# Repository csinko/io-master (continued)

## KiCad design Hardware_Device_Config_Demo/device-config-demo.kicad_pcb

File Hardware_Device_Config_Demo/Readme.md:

# Device Configuration Demo Board

A board to demonstrate the parts of the overall design that need to be configured when setting up a protocol for operation.

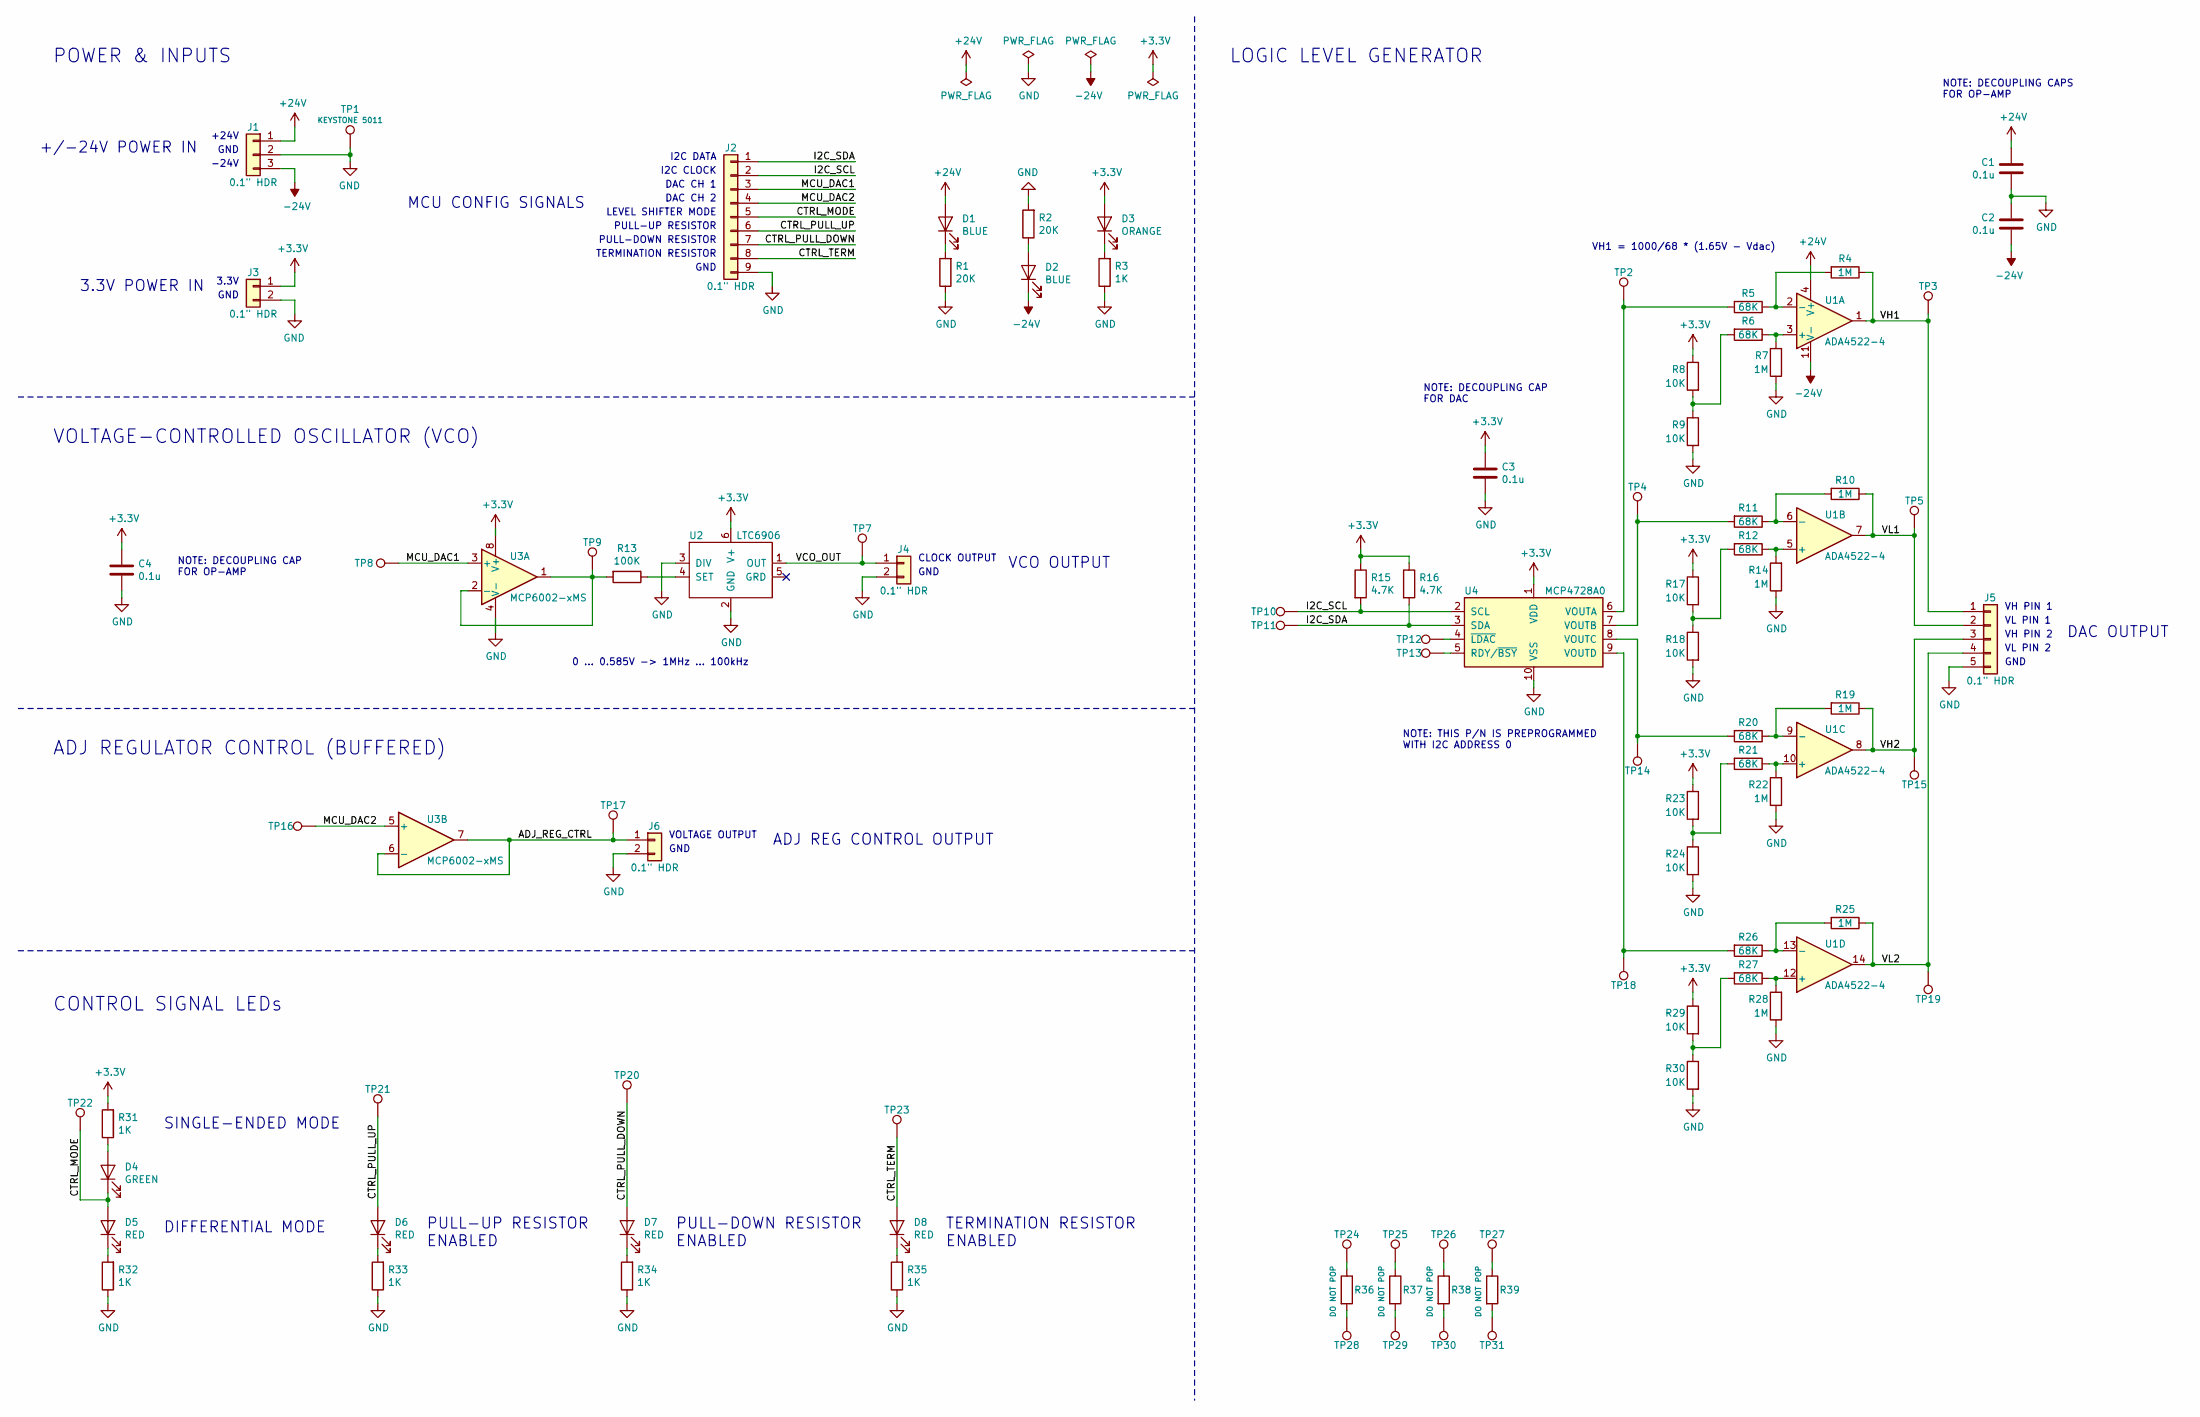
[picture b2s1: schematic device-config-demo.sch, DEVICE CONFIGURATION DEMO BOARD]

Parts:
C1, C2, C3, C4: 0.1u; C_0603_1608Metric
D1, D2: BLUE; LED_0603_1608Metric
D3: ORANGE; LED_0603_1608Metric
D4: GREEN; LED_0603_1608Metric
D5, D6, D7, D8: RED; LED_0603_1608Metric
J1: 0.1\" HDR; PinHeader_1x03_P2.54mm_Vertical
J2: 0.1\" HDR; PinHeader_1x09_P2.54mm_Vertical
J3, J4, J6: 0.1\" HDR; PinHeader_1x02_P2.54mm_Vertical
J5: 0.1\" HDR; PinHeader_1x05_P2.54mm_Vertical
R1, R2: 20K; R_0603_1608Metric
R3, R31, R32, R33, R34, R35: 1K; R_0603_1608Metric
R4, R7, R10, R14, R19, R22, R25, R28: 1M; R_0603_1608Metric
R5, R6, R11, R12, R20, R21, R26, R27: 68K; R_0603_1608Metric
R8, R9, R17, R18, R23, R24, R29, R30: 10K; R_0603_1608Metric
R13: 100K; R_0603_1608Metric
R15, R16: 4.7K; R_0603_1608Metric
R36, R37, R38, R39: R; R_0603_1608Metric
TP1: GND; TestPoint_Keystone_5010-5014_Multipurpose
TP2: DAC_A; TestPoint_THTPad_D1.0mm_Drill0.5mm
TP3: VH1; TestPoint_THTPad_D1.0mm_Drill0.5mm
TP4: DAC_B; TestPoint_THTPad_D1.0mm_Drill0.5mm
TP5: VL1; TestPoint_THTPad_D1.0mm_Drill0.5mm
TP7: VCO_OUT; TestPoint_THTPad_D1.0mm_Drill0.5mm
TP8: MCU_DAC1; TestPoint_THTPad_D1.0mm_Drill0.5mm
TP9: VCO_SET; TestPoint_THTPad_D1.0mm_Drill0.5mm
TP10: I2C_SCL; TestPoint_THTPad_D1.0mm_Drill0.5mm
TP11: I2C_SDA; TestPoint_THTPad_D1.0mm_Drill0.5mm
TP12: DAC_LDAC; TestPoint_THTPad_D1.0mm_Drill0.5mm
TP13: DAC_RDY; TestPoint_THTPad_D1.0mm_Drill0.5mm
TP14: DAC_C; TestPoint_THTPad_D1.0mm_Drill0.5mm
TP15: VH2; TestPoint_THTPad_D1.0mm_Drill0.5mm
TP16: MCU_DAC2; TestPoint_THTPad_D1.0mm_Drill0.5mm
TP17: ADJ_REG_CTRL; TestPoint_THTPad_D1.0mm_Drill0.5mm
TP18: DAC_D; TestPoint_THTPad_D1.0mm_Drill0.5mm
TP19: VL2; TestPoint_THTPad_D1.0mm_Drill0.5mm
TP20: CTRL_PULL_DOWN; TestPoint_THTPad_D1.0mm_Drill0.5mm
TP21: CTRL_PULL_UP; TestPoint_THTPad_D1.0mm_Drill0.5mm
TP22: CTRL_MODE; TestPoint_THTPad_D1.0mm_Drill0.5mm
TP23: CTRL_TERM; TestPoint_THTPad_D1.0mm_Drill0.5mm
TP24, TP25, TP26, TP27, TP28, TP29, TP30, TP31: TestPoint; TestPoint_THTPad_D1.0mm_Drill0.5mm
U1: ADA4522-4; TSSOP-14_4.4x5mm_P0.65mm
U2: LTC6906; TSOT-23-6
U3: MCP6002-xMS; MSOP-8_3x3mm_P0.65mm
U4: MCP4728A0; MSOP-10_3x3mm_P0.5mm

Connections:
+3V3: C3.1, C4.1, D3.2 (A), J3.1, R8.1, R15.1, R16.1, R17.1, R23.1, R29.1, R31.2, U2.6 (V+), U3.8 (V+), U4.1 (VDD)
+24V: C1.1, D1.2 (A), J1.1, U1.4 (V+)
-24V: C2.2, D2.1 (K), J1.3, U1.11 (V-)
/ADJ_REG_CTRL: J6.1, TP17.1, U3.6 (-), U3.7
/CTRL_MODE: D4.1 (K), D5.2 (A), J2.5, TP22.1
/CTRL_PULL_DOWN: D7.2 (A), J2.7, TP20.1
/CTRL_PULL_UP: D6.2 (A), J2.6, TP21.1
/CTRL_TERM: D8.2 (A), J2.8, TP23.1
/I2C_SCL: J2.2, R15.2, TP10.1, U4.2 (SCL)
/I2C_SDA: J2.1, R16.2, TP11.1, U4.3 (SDA)
/MCU_DAC1: J2.3, TP8.1, U3.3 (+)
/MCU_DAC2: J2.4, TP16.1, U3.5 (+)
/VCO_OUT: J4.1, TP7.1, U2.1 (OUT)
/VH1: J5.1, R4.1, TP3.1, U1.1
/VH2: J5.3, R19.1, TP15.1, U1.8
/VL1: J5.2, R10.1, TP5.1, U1.7
/VL2: J5.4, R25.1, TP19.1, U1.14
GND: C1.2, C2.1, C3.2, C4.2, J1.2, J2.9, J3.2, J4.2, J5.5, J6.2, R1.1, R2.2, R3.1, R7.1, R9.2, R14.1, R18.2, R22.1, R24.2, R28.1, R30.2, R32.1, R33.1, R34.1, R35.1, TP1.1, U2.2 (GND), U2.3 (DIV), U3.4 (V-), U4.10 (VSS)
unnamed: D1.1 (K), R1.2
unnamed: D2.2 (A), R2.1
unnamed: D3.1 (K), R3.2
unnamed: D4.2 (A), R31.1
unnamed: D5.1 (K), R32.2
unnamed: D6.1 (K), R33.2
unnamed: D7.1 (K), R34.2
unnamed: D8.1 (K), R35.2
unnamed: R4.2, R5.1, U1.2 (-)
unnamed: R5.2, TP2.1, U4.6 (VOUTA)
unnamed: R6.1, R7.2, U1.3 (+)
unnamed: R6.2, R8.2, R9.1
unnamed: R10.2, R11.1, U1.6 (-)
unnamed: R11.2, TP4.1, U4.7 (VOUTB)
unnamed: R12.1, R14.2, U1.5 (+)
unnamed: R12.2, R17.2, R18.1
unnamed: R13.1, U2.4 (SET)
unnamed: R13.2, TP9.1, U3.1, U3.2 (-)
unnamed: R19.2, R20.1, U1.9 (-)
unnamed: R20.2, TP14.1, U4.8 (VOUTC)
unnamed: R21.1, R22.2, U1.10 (+)
unnamed: R21.2, R23.2, R24.1
unnamed: R25.2, R26.1, U1.13 (-)
unnamed: R26.2, TP18.1, U4.9 (VOUTD)
unnamed: R27.1, R28.2, U1.12 (+)
unnamed: R27.2, R29.2, R30.1
unnamed: R36.1, TP24.1
unnamed: R36.2, TP28.1
unnamed: R37.1, TP25.1
unnamed: R37.2, TP29.1
unnamed: R38.1, TP26.1
unnamed: R38.2, TP30.1
unnamed: R39.1, TP27.1
unnamed: R39.2, TP31.1
unnamed: TP12.1, U4.4 (~LDAC)
unnamed: TP13.1, U4.5 (RDY/~BSY)

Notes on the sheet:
LOGIC LEVEL GENERATOR
NOTE: DECOUPLING CAP FOR DAC
VH1 = 1000/68 * (1.65V - Vdac)
NOTE: DECOUPLING CAPS FOR OP-AMP
NOTE: THIS P/N IS PREPROGRAMMED WITH I2C ADDRESS 0
VH PIN 1
VL PIN 1
VH PIN 2
VL PIN 2
DAC OUTPUT
+/-24V POWER IN
3.3V POWER IN
LEVEL SHIFTER MODE
PULL-UP RESISTOR
PULL-DOWN RESISTOR
TERMINATION RESISTOR
MCU CONFIG SIGNALS
TERMINATION RESISTOR ENABLED
PULL-DOWN RESISTOR ENABLED
PULL-UP RESISTOR ENABLED
SINGLE-ENDED MODE
DIFFERENTIAL MODE
I2C DATA
I2C CLOCK
GND
VOLTAGE-CONTROLLED OSCILLATOR (VCO)
NOTE: DECOUPLING CAP FOR OP-AMP
0 ... 0.585V -> 1MHz ... 100kHz
+24V
-24V
3.3V
DAC CH 1
DAC CH 2
ADJ REGULATOR CONTROL (BUFFERED)
CONTROL SIGNAL LEDs
POWER & INPUTS
VCO OUTPUT
CLOCK OUTPUT
ADJ REG CONTROL OUTPUT
VOLTAGE OUTPUT

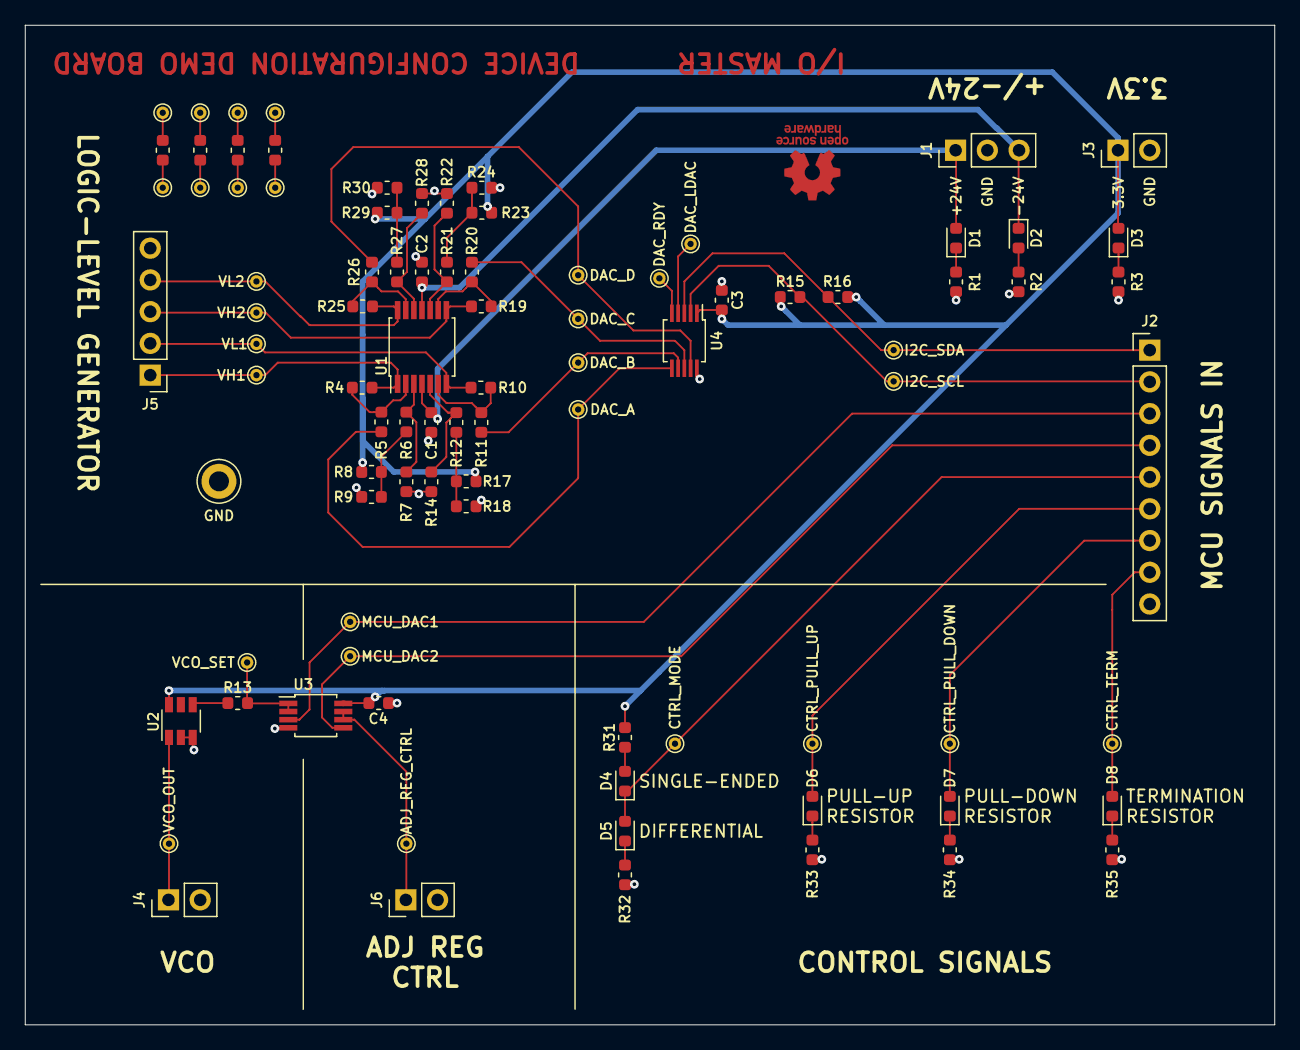
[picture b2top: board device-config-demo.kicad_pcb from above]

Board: 2 copper layers, 100.0 x 80.0 mm, 91 parts (0 on the bottom side), 54 nets.

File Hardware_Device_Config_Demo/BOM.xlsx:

Device Configuration Demo Board - Populated Parts
Qty. | Refdes. | Description | Manufacturer | Manufacturer PN | Digikey PN | Unit Price | Extended Price
1.0 | PCB1 | bare pcb, 2 layer, 1 oz copper, green soldermask, 50x75mm | JLCPCB |  |  | 0.8 | 0.8
4.0 | C1, C2, C3, C4 | 0.1u capacitor, ceramic, 50V 10%, X7R, 0603 | Samsung | CL10B104KB8NNNL | 1276-CL10B104KB8NNNLCT-ND | 0.1 | 0.4
2.0 | D1, D2 | blue led, Vf=3.2V, 0603 | Wurth | 150060BS75000 | 732-4966-1-ND | 0.16 | 0.32
1.0 | D3 | orange led, Vf=2V, 0603 | Lite-On | LTST-C190KFKT | 160-1434-1-ND | 0.24 | 0.24
1.0 | D4 | green led, Vf=2V, 0603 | Wurth | 150060VS75000 | 732-4980-1-ND | 0.16 | 0.16
4.0 | D5, D6, D7, D8 | red led, Vf=1.9V, 0603 | Wurth | 150060SS75000‎ | 732-4979-1-ND | 0.14 | 0.56
1.0 | J1 | 3 pin header, 0.1", vertical, through hole | Sullins | PREC003SAAN-RC | S1012EC-03-ND | 0.16 | 0.16
1.0 | J2 | 9 pin header, 0.1", vertical, through hole | Sullins | ‎PREC009SAAN-RC | S1012EC-09-ND | 0.21 | 0.21
3.0 | J3, J4, J6 | 2 pin header, 0.1", vertical, through hole | Sullins | PREC002SAAN-RC | S1012EC-02-ND | 0.16 | 0.48
1.0 | J5 | 5 pin header, 0.1", vertical, through hole | Sullins | PREC005SAAN-RC‎ | S1012EC-05-ND | 0.15 | 0.15
2.0 | R1, R2 | 20K resistor, 1%, 1/10W, 0603 | Vishay Dale | CRCW060320K0FKEC‎ | 541-2993-1-ND | 0.1 | 0.2
6.0 | R3, R31, R32, R33, R34, R35 | 1K resistor, 1%, 1/10W, 0603 | Vishay Dale | CRCW06031K00FKEA‎ | 541-1.00KHCT-ND | 0.1 | 0.6
8.0 | R4, R7, R10, R14, R19, R22, R25, R28 | 1M resistor, 1%, 1/10W, 0603 | Vishay Dale | CRCW06031M00FKEA‎ | 541-1.00MHCT-ND | 0.1 | 0.8
8.0 | R5, R6, R11, R12, R20, R21, R26, R27 | 68K resistor, 1%, 1/10W, 0603 | Vishay Dale | CRCW060368K0FKEA‎ | 541-68.0KHCT-ND | 0.1 | 0.8
8.0 | R8, R9, R17, R18, R23, R24, R29, R30 | 10K resistor, 1%, 1/10W, 0603 | Vishay Dale | CRCW060310K0FKEA | 541-10.0KHCT-ND | 0.1 | 0.8
1.0 | R13 | 100K resistor, 1%, 1/10W, 0603 | Vishay Dale | CRCW0603100KFKEA‎ | 541-100KHCT-ND | 0.1 | 0.1
2.0 | R15, R16 | 4.7K resistor, 1%, 1/10W, 0603 | Vishay Dale | CRCW06034K70FKEA‎ | 541-4.70KHCT-ND | 0.1 | 0.2
1.0 | TP1 | multipurpose test point loop | Keystone | 5011 | 36-5011-ND | 0.35 | 0.35
1.0 | U1 | quad op-amp, rail to rail, 50V, 14-TSSOP | Analog Devices | ADA4522-4ARUZ | ADA4522-4ARUZ-ND | 8.45 | 8.45
1.0 | U2 | voltage controlled oscillator, 1kHz to 1MHz, SOT-23-6 | Analog Devices | LTC6906 | LTC6906CS6#TRPBFCT-ND | 3.13 | 3.13
1.0 | U3 | dual op-amp, rail to rail, 8-MSOP | Microchip | ‎MCP6002 | MCP6002T-I/MSCT-ND | 0.33 | 0.33
1.0 | U4 | dac, 12-bit, 2 channel, I2C, 10-MSOP | Microchip | ‎MCP4728A0 | MCP4728A0T-E/UNCT-ND | 1.89 | 1.89
 |  |  |  |  |  | BOM Total | 20.33

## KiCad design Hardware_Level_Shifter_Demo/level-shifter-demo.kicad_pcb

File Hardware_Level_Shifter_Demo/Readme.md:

# Level Shifter Demo Board

A board to demonstrate the level shifter subsystem.

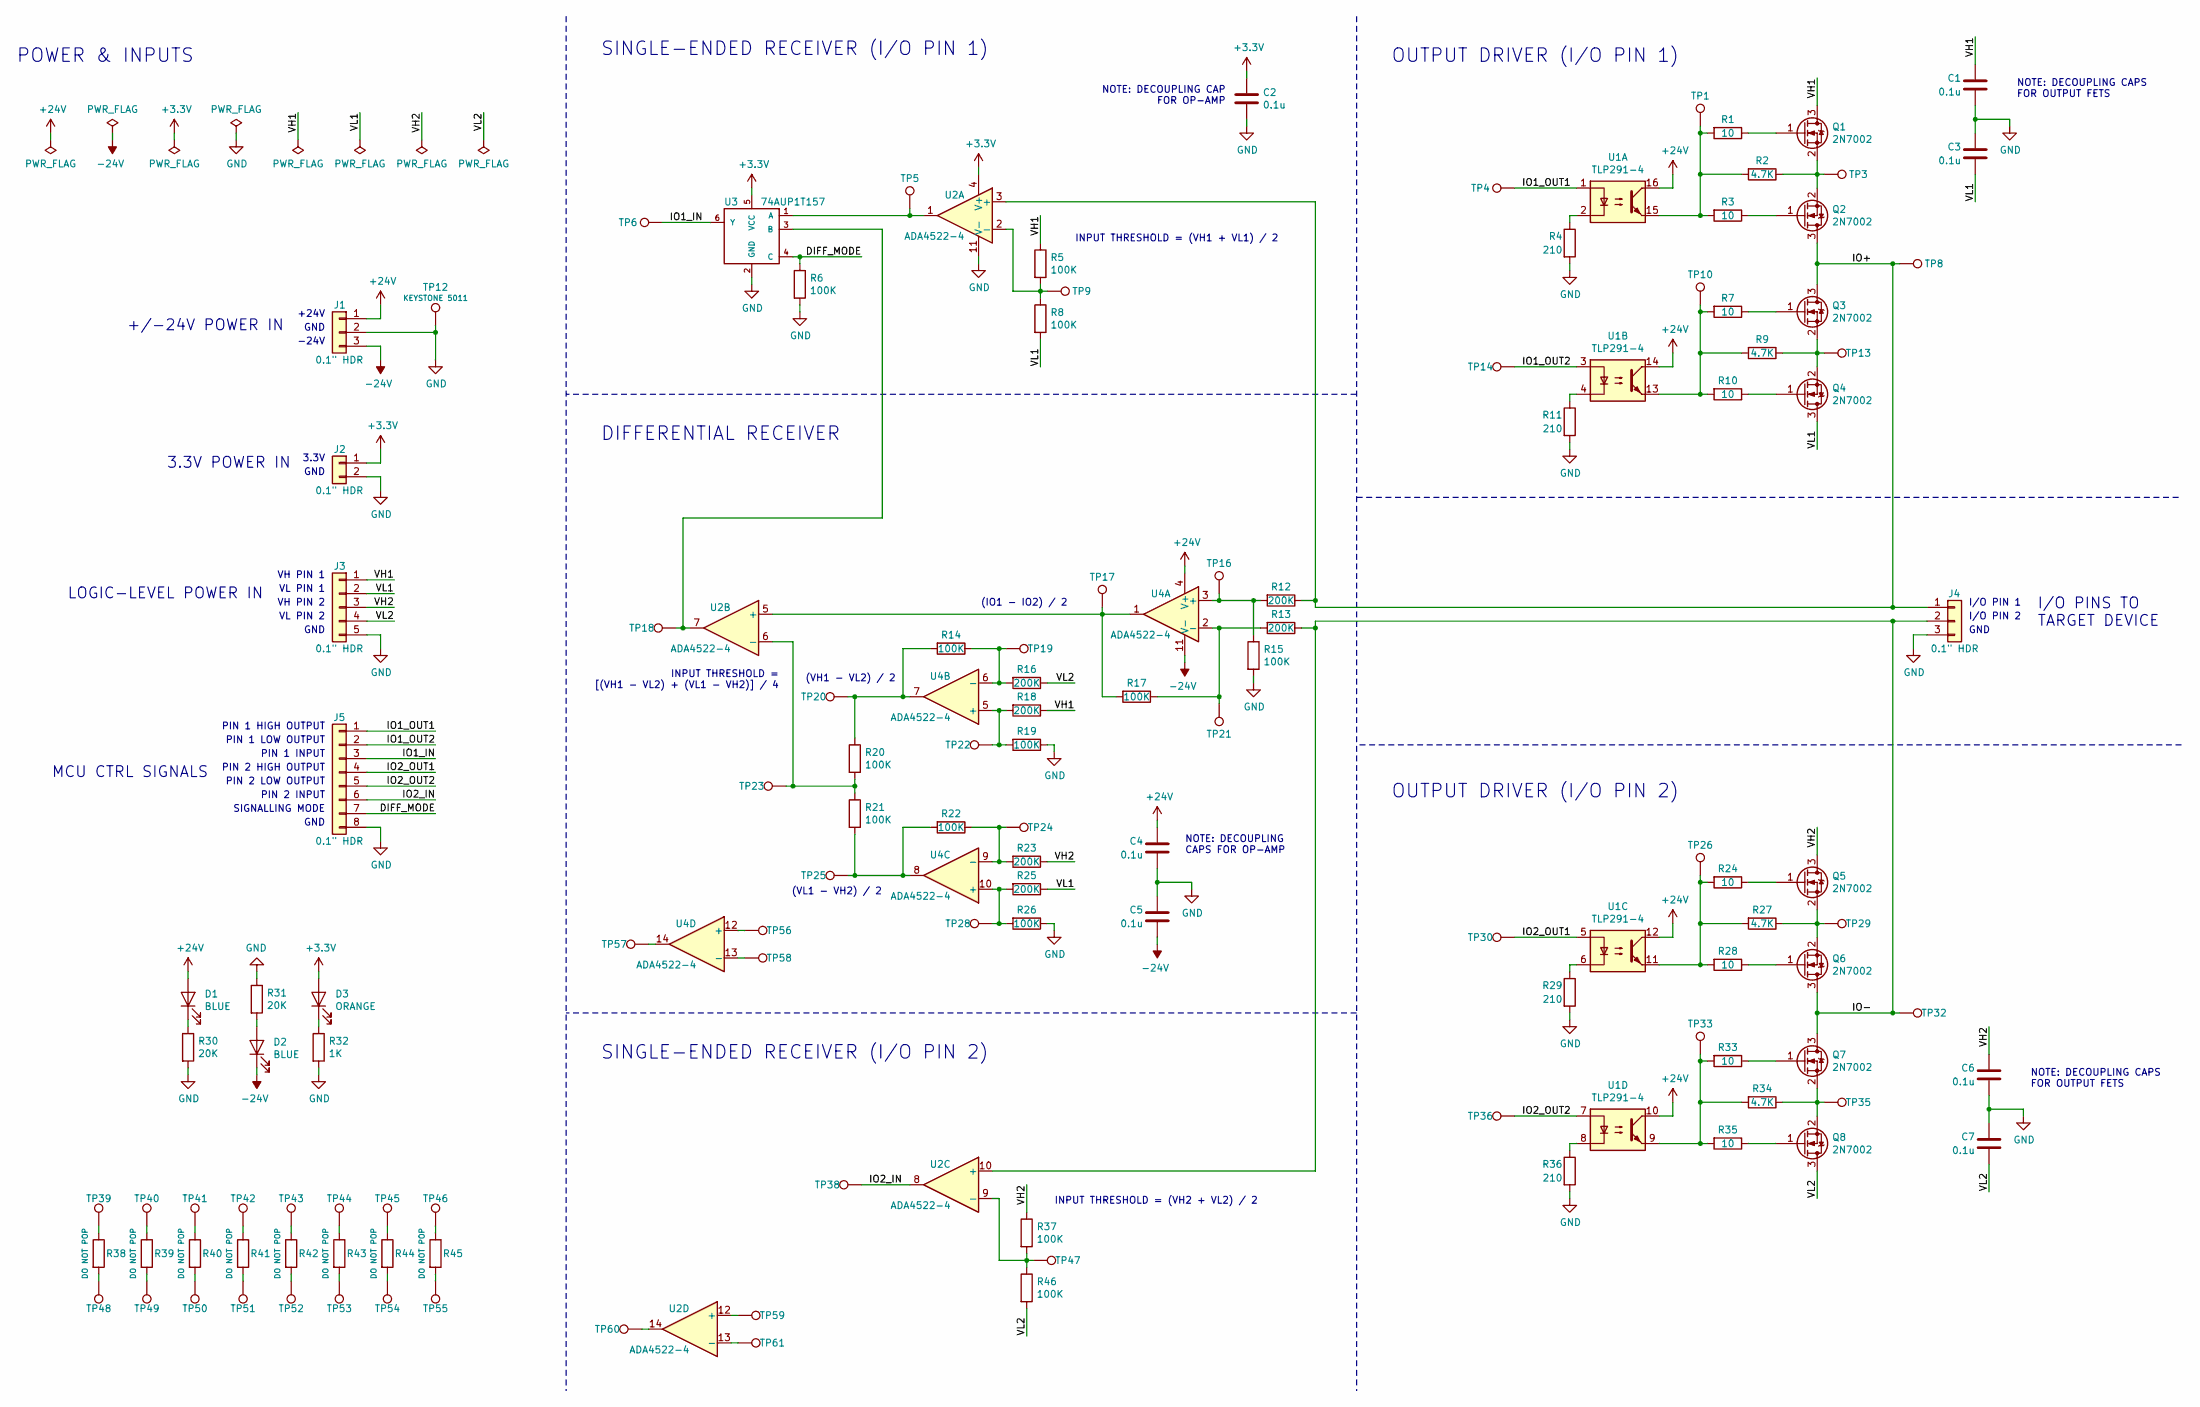
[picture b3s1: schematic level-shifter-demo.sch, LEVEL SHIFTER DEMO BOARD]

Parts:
C1, C2, C3, C4, C5, C6, C7: 0.1u; C_0603_1608Metric
D1, D2: BLUE; LED_0603_1608Metric
D3: ORANGE; LED_0603_1608Metric
J1, J4: 0.1\" HDR; PinSocket_1x03_P2.54mm_Vertical
J2: 0.1\" HDR; PinSocket_1x02_P2.54mm_Vertical
J3: 0.1\" HDR; PinSocket_1x05_P2.54mm_Vertical
J5: 0.1\" HDR; PinSocket_1x08_P2.54mm_Vertical
Q1, Q2, Q3, Q4, Q5, Q6, Q7, Q8: 2N7002; SOT-23
R1, R3, R7, R10, R24, R28, R33, R35: 10; R_0603_1608Metric
R2, R9, R27, R34: 4.7K; R_0603_1608Metric
R4, R11, R29, R36: 210; R_0603_1608Metric
R5, R6, R8, R14, R15, R17, R19, R20, R21, R22, R26, R37, R46: 100K; R_0603_1608Metric
R12, R13, R16, R18, R23, R25: 200K; R_0603_1608Metric
R30, R31: 20K; R_0603_1608Metric
R32: 1K; R_0603_1608Metric
R38, R39, R40, R41, R42, R43, R44, R45: R; R_0603_1608Metric
TP1, TP3, TP5, TP9, TP10, TP13, TP16, TP17, TP18, TP19, TP20, TP21, TP22, TP23, TP24, TP25, TP26, TP28, TP29, TP33, TP35, TP39, TP40, TP41, TP42, TP43, TP44, TP45, TP46, TP47, TP48, TP49, TP50, TP51, TP52, TP53, TP54, TP55, TP56, TP57, TP58, TP59, TP60, TP61: TestPoint; TestPoint_THTPad_D1.0mm_Drill0.5mm
TP4: IO1_OUT1; TestPoint_THTPad_D1.0mm_Drill0.5mm
TP6: IO1_IN; TestPoint_THTPad_D1.0mm_Drill0.5mm
TP8: IO1; TestPoint_THTPad_D1.0mm_Drill0.5mm
TP12: GND; TestPoint_Keystone_5010-5014_Multipurpose
TP14: IO1_OUT2; TestPoint_THTPad_D1.0mm_Drill0.5mm
TP30: IO2_OUT1; TestPoint_THTPad_D1.0mm_Drill0.5mm
TP32: IO2; TestPoint_THTPad_D1.0mm_Drill0.5mm
TP36: IO2_OUT2; TestPoint_THTPad_D1.0mm_Drill0.5mm
TP38: IO2_IN; TestPoint_THTPad_D1.0mm_Drill0.5mm
U1: TLP291-4; SOIC-16_4.55x10.3mm_P1.27mm
U2, U4: ADA4522-4; TSSOP-14_4.4x5mm_P0.65mm
U3: 74AUP1T157; SOT-363_SC-70-6

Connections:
+3V3: C2.1, D3.2 (A), J2.1, U2.4 (V+), U3.5 (VCC)
+24V: C4.1, D1.2 (A), J1.1, U1.10, U1.12, U1.14, U1.16, U4.4 (V+)
-24V: C5.2, D2.1 (K), J1.3, U4.11 (V-)
/DIFF_MODE: J5.7, R6.1, U3.4 (C)
/IO1_IN: J5.3, TP6.1, U3.6 (Y)
/IO1_OUT1: J5.1, TP4.1, U1.1
/IO1_OUT2: J5.2, TP14.1, U1.3
/IO2_IN: J5.6, TP38.1, U2.8
/IO2_OUT1: J5.4, TP30.1, U1.5
/IO2_OUT2: J5.5, TP36.1, U1.7
/IO+: J4.1, Q2.3 (D), Q3.3 (D), R12.1, TP8.1, U2.3 (+)
/IO-: J4.2, Q6.3 (D), Q7.3 (D), R13.1, TP32.1, U2.10 (+)
/VH1: C1.1, J3.1, Q1.3 (D), R5.1, R18.1
/VH2: C6.1, J3.3, Q5.3 (D), R23.1, R37.1
/VL1: C3.2, J3.2, Q4.3 (D), R8.2, R25.1
/VL2: C7.2, J3.4, Q8.3 (D), R16.1, R46.2
GND: C1.2, C2.2, C3.1, C4.2, C5.1, C6.2, C7.1, J1.2, J2.2, J3.5, J4.3, J5.8, R4.2, R6.2, R11.2, R15.2, R19.1, R26.1, R29.2, R30.2, R31.1, R32.2, R36.2, TP12.1, U2.11 (V-), U3.2 (GND)
unnamed: D1.1 (K), R30.1
unnamed: D2.2 (A), R31.2
unnamed: D3.1 (K), R32.1
unnamed: Q1.1 (G), R1.1
unnamed: Q1.2 (S), Q2.2 (S), R2.1, TP3.1
unnamed: Q2.1 (G), R3.1
unnamed: Q3.1 (G), R7.1
unnamed: Q3.2 (S), Q4.2 (S), R9.1, TP13.1
unnamed: Q4.1 (G), R10.1
unnamed: Q5.1 (G), R24.1
unnamed: Q5.2 (S), Q6.2 (S), R27.1, TP29.1
unnamed: Q6.1 (G), R28.1
unnamed: Q7.1 (G), R33.1
unnamed: Q7.2 (S), Q8.2 (S), R34.1, TP35.1
unnamed: Q8.1 (G), R35.1
unnamed: R1.2, R2.2, R3.2, TP1.1, U1.15
unnamed: R4.1, U1.2
unnamed: R5.2, R8.1, TP9.1, U2.2 (-)
unnamed: R7.2, R9.2, R10.2, TP10.1, U1.13
unnamed: R11.1, U1.4
unnamed: R12.2, R15.1, TP16.1, U4.3 (+)
unnamed: R13.2, R17.1, TP21.1, U4.2 (-)
unnamed: R14.1, R16.2, TP19.1, U4.6 (-)
unnamed: R14.2, R20.1, TP20.1, U4.7
unnamed: R17.2, TP17.1, U2.5 (+), U4.1
unnamed: R18.2, R19.2, TP22.1, U4.5 (+)
unnamed: R20.2, R21.1, TP23.1, U2.6 (-)
unnamed: R21.2, R22.2, TP25.1, U4.8
unnamed: R22.1, R23.2, TP24.1, U4.9 (-)
unnamed: R24.2, R27.2, R28.2, TP26.1, U1.11
unnamed: R25.2, R26.2, TP28.1, U4.10 (+)
unnamed: R29.1, U1.6
unnamed: R33.2, R34.2, R35.2, TP33.1, U1.9
unnamed: R36.1, U1.8
unnamed: R37.2, R46.1, TP47.1, U2.9 (-)
unnamed: R38.1, TP39.1
unnamed: R38.2, TP48.1
unnamed: R39.1, TP40.1
unnamed: R39.2, TP49.1
unnamed: R40.1, TP41.1
unnamed: R40.2, TP50.1
unnamed: R41.1, TP42.1
unnamed: R41.2, TP51.1
unnamed: R42.1, TP43.1
unnamed: R42.2, TP52.1
unnamed: R43.1, TP44.1
unnamed: R43.2, TP53.1
unnamed: R44.1, TP45.1
unnamed: R44.2, TP54.1
unnamed: R45.1, TP46.1
unnamed: R45.2, TP55.1
unnamed: TP5.1, U2.1, U3.1 (A)
unnamed: TP18.1, U2.7, U3.3 (B)
unnamed: TP56.1, U4.12 (+)
unnamed: TP57.1, U4.14
unnamed: TP58.1, U4.13 (-)
unnamed: TP59.1, U2.12 (+)
unnamed: TP60.1, U2.14
unnamed: TP61.1, U2.13 (-)

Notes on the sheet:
OUTPUT DRIVER (I/O PIN 1)
OUTPUT DRIVER (I/O PIN 2)
INPUT THRESHOLD = (VH1 + VL1) / 2
DIFFERENTIAL RECEIVER
SINGLE-ENDED RECEIVER (I/O PIN 1)
SINGLE-ENDED RECEIVER (I/O PIN 2)
(IO1 - IO2) / 2
(VH1 - VL2) / 2
INPUT THRESHOLD = [(VH1 - VL2) + (VL1 - VH2)] / 4
(VL1 - VH2) / 2
NOTE: DECOUPLING CAP FOR OP-AMP
POWER & INPUTS
+24V
GND
-24V
3.3V
VH PIN 1
VL PIN 1
VH PIN 2
VL PIN 2
+/-24V POWER IN
3.3V POWER IN
LOGIC-LEVEL POWER IN
MCU CTRL SIGNALS
PIN 1 HIGH OUTPUT
PIN 1 LOW OUTPUT
PIN 1 INPUT
PIN 2 HIGH OUTPUT
PIN 2 LOW OUTPUT
PIN 2 INPUT
SIGNALLING MODE
I/O PIN 1
I/O PIN 2
I/O PINS TO TARGET DEVICE
NOTE: DECOUPLING CAPS FOR OUTPUT FETS
INPUT THRESHOLD = (VH2 + VL2) / 2
NOTE: DECOUPLING CAPS FOR OP-AMP

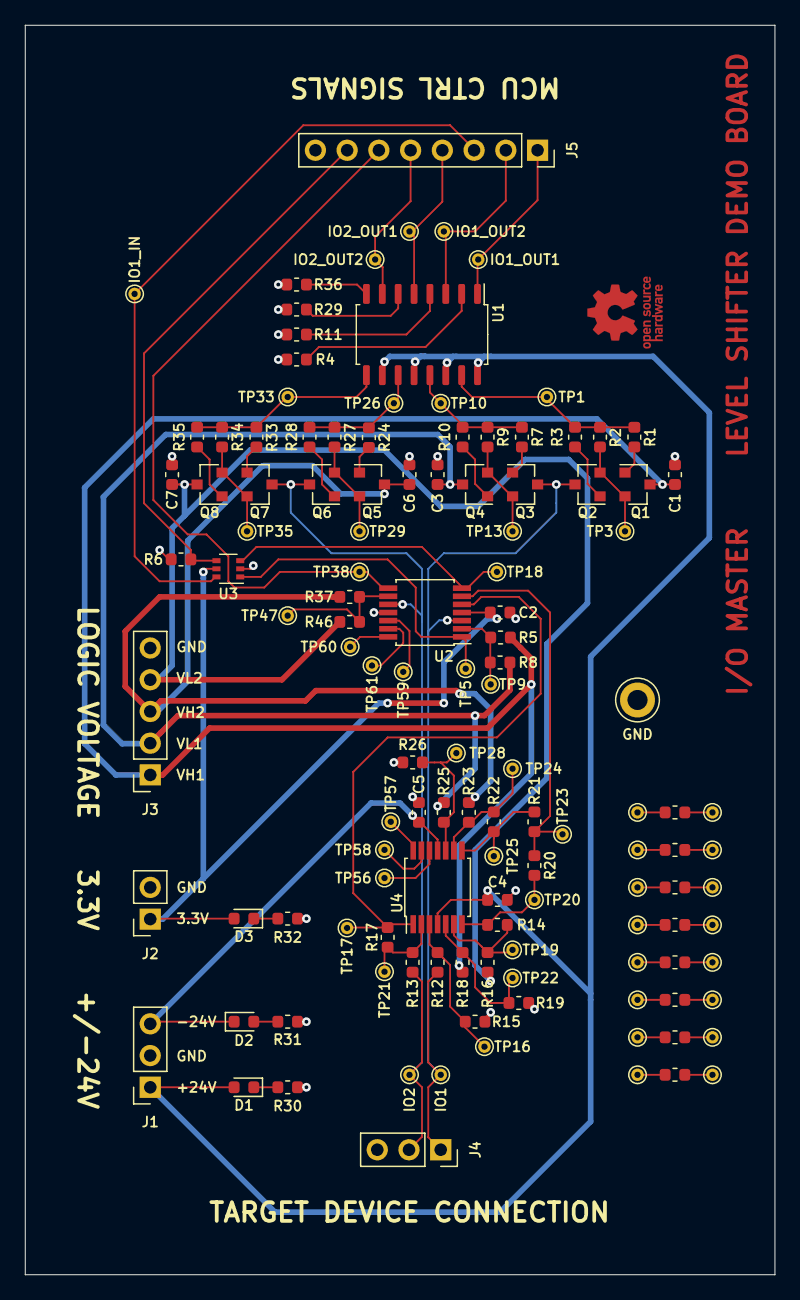
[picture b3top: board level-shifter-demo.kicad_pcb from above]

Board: 2 copper layers, 60.0 x 100.0 mm, 126 parts (0 on the bottom side), 76 nets.

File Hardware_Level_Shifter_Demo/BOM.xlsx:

Level Shifter Demo Board - Populated Parts
Qty. | Refdes. | Description | Manufacturer | Manufacturer PN | Digikey PN | Unit Price | Extended Price
7.0 | C1, C2, C3, C4, C5, C6, C7 | 0.1u capacitor, ceramic, 50V 10%, X7R, 0603 | Samsung | CL10B104KB8NNNL | 1276-CL10B104KB8NNNLCT-ND | 0.1 | 0.7
2.0 | D1, D2 | blue led, Vf=3.2V, 0603 | Wurth | 150060BS75000 | 732-4966-1-ND | 0.16 | 0.32
1.0 | D3 | orange led, Vf=2V, 0603 | Lite-On | LTST-C190KFKT | 160-1434-1-ND | 0.24 | 0.24
2.0 | J1, J4 | 3 pin header, 0.1", vertical, through hole | Sullins | PREC003SAAN-RC | S1012EC-03-ND | 0.16 | 0.32
1.0 | J2 | 2 pin header, 0.1", vertical, through hole | Sullins | PREC002SAAN-RC | S1012EC-02-ND | 0.16 | 0.16
1.0 | J3 | 5 pin header, 0.1", vertical, through hole | Sullins | PREC005SAAN-RC‎ | S1012EC-05-ND | 0.15 | 0.15
1.0 | J5 | 8 pin header, 0.1", vertical, through hole | Sullins | ‎PREC008SAAN-RC‎ | S1012EC-08-ND | 0.19 | 0.19
8.0 | Q1, Q2, Q3, Q4, Q5, Q6, Q7, Q8 | n-channel MOSFET, 60V, 300mA, SOT-23-3 | Nexperia | 2N7002,215 | 1727-2764-1-ND | 0.177 | 1.416
8.0 | R1, R3, R7, R10, R24, R28, R33, R35 | 10ohm resistor, 1%, 1/10W, 0603 | Vishay Dale | CRCW060310R0FKEAC‎ | 541-3952-1-ND | 0.1 | 0.8
4.0 | R2, R9, R27, R34 | 4.7K resistor, 1%, 1/10W, 0603 | Vishay Dale | CRCW06034K70FKEA‎ | 541-4.70KHCT-ND | 0.1 | 0.4
4.0 | R4, R11, R29, R36 | 210ohm resistor, 1%, 1/10W, 0603 | Vishay Dale | CRCW0603210RFKEA‎ | 541-210HCT-ND | 0.1 | 0.4
13.0 | R5, R6, R8, R14, R15, R17, R19, R20, R21, R22, R26, R37, R46 | 100K resistor, 1%, 1/10W, 0603 | Vishay Dale | CRCW0603100KFKEA‎ | 541-100KHCT-ND | 0.1 | 1.3
6.0 | R12, R13, R16, R18, R23, R25 | 200K resistor, 1%, 1/10W, 0603 | Vishay Dale | CRCW0603200KFKEAC‎ | 541-4027-1-ND | 0.1 | 0.6
2.0 | R30, R31 | 20K resistor, 1%, 1/10W, 0603 | Vishay Dale | CRCW060320K0FKEC‎ | 541-2993-1-ND | 0.1 | 0.2
1.0 | R32 | 1K resistor, 1%, 1/10W, 0603 | Vishay Dale | CRCW06031K00FKEA‎ | 541-1.00KHCT-ND | 0.1 | 0.1
1.0 | TP12 | multipurpose test point loop | Keystone | 5011 | 36-5011-ND | 0.35 | 0.35
1.0 | U1 | optoisolator, 4 channel, 16-SOIC | Toshiba | TLP291-4(GB,E)‎ | TLP291-4(GBE)-ND | 1.04 | 1.04
2.0 | U2, U4 | quad op-amp, rail to rail, 50V, 14-TSSOP | Analog Devices | ADA4522-4ARUZ | ADA4522-4ARUZ-ND | 8.45 | 16.9
1.0 | U3 | 2 channel mux, schmitt trigger, SC-70-6 | Texas Instruments | SN74AUP1T157DCKR‎ | 296-27393-1-ND | 0.37 | 0.37
 |  |  |  |  |  | BOM Total | 25.956

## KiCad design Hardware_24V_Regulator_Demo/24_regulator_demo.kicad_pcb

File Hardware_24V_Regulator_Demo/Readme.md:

# +/-24V Regulator Demo Board

A board to demonstrate the dual rail 24V regulator with an input voltage range of 5-12V.

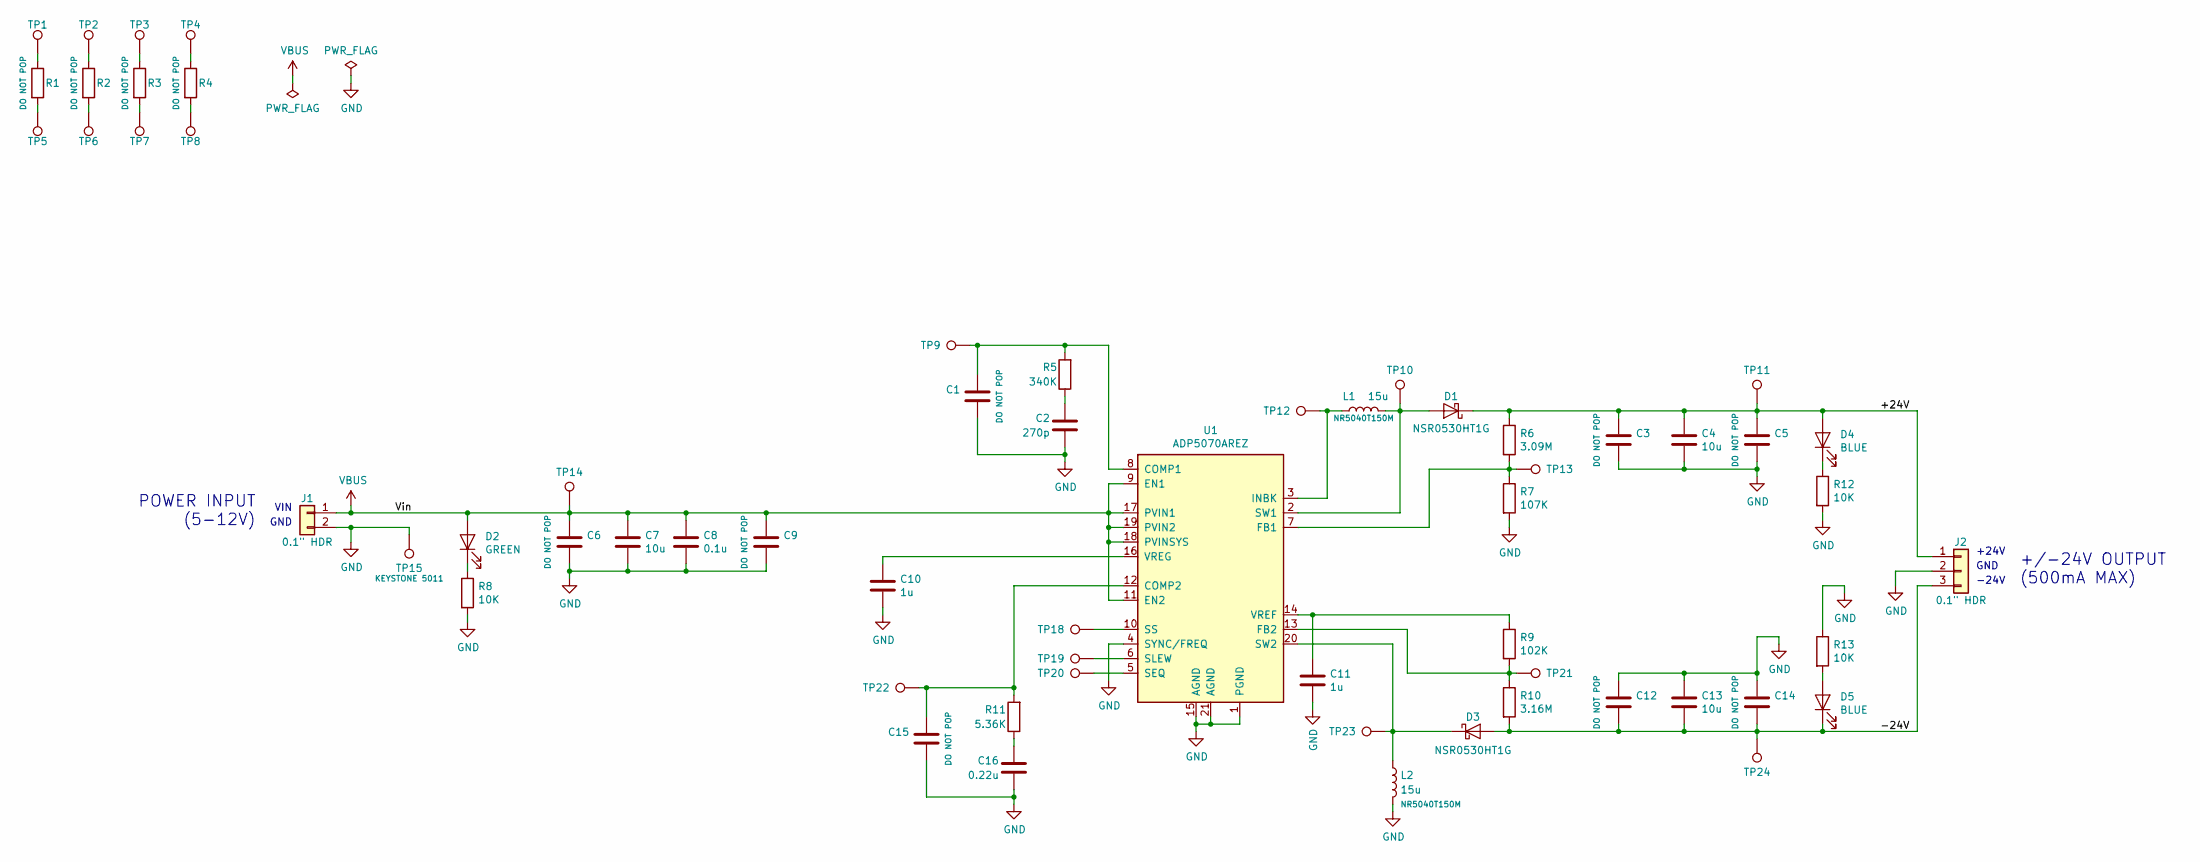
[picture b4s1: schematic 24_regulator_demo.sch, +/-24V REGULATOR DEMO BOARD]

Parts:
C1, C5, C9, C14, C15: C; C_0603_1608Metric
C2: 270p; C_0603_1608Metric
C3, C6, C12: C; C_1206_3216Metric
C4, C7, C13: 10u; C_1206_3216Metric
C8: 0.1u; C_0603_1608Metric
C10, C11: 1u; C_1206_3216Metric
C16: 0.22u; C_0603_1608Metric
D1, D3: NSR0530HT1G; D_SOD-323
D2: GREEN; LED_0603_1608Metric
D4, D5: BLUE; LED_0603_1608Metric
J1: 0.1\" HDR; PinHeader_1x02_P2.54mm_Vertical
J2: 0.1\" HDR; PinHeader_1x03_P2.54mm_Vertical
L1, L2: 15u; L_Murata_DEM80xxC
R1, R2, R3, R4: R; R_0603_1608Metric_Pad1.05x0.95mm_HandSolder
R5: 340K; R_0603_1608Metric
R6: 3.09M; R_0603_1608Metric
R7: 107K; R_0603_1608Metric
R8, R12, R13: 10K; R_0603_1608Metric
R9: 102K; R_0603_1608Metric
R10: 3.16M; R_0603_1608Metric
R11: 5.36K; R_0603_1608Metric
TP1, TP2, TP3, TP4, TP5, TP6, TP7, TP8: TestPoint; TestPoint_THTPad_D1.0mm_Drill0.5mm
TP9: COMP1; TestPoint_THTPad_D1.0mm_Drill0.5mm
TP10: SW1; TestPoint_THTPad_D1.0mm_Drill0.5mm
TP11: +24V; TestPoint_THTPad_D1.0mm_Drill0.5mm
TP12: INBK; TestPoint_THTPad_D1.0mm_Drill0.5mm
TP13: FB1; TestPoint_THTPad_D1.0mm_Drill0.5mm
TP14: VIN; TestPoint_THTPad_D1.0mm_Drill0.5mm
TP15: GND; TestPoint_Keystone_5010-5014_Multipurpose
TP18: SS; TestPoint_THTPad_D1.0mm_Drill0.5mm
TP19: SLEW; TestPoint_THTPad_D1.0mm_Drill0.5mm
TP20: SEQ; TestPoint_THTPad_D1.0mm_Drill0.5mm
TP21: FB2; TestPoint_THTPad_D1.0mm_Drill0.5mm
TP22: COMP2; TestPoint_THTPad_D1.0mm_Drill0.5mm
TP23: SW2; TestPoint_THTPad_D1.0mm_Drill0.5mm
TP24: -24V; TestPoint_THTPad_D1.0mm_Drill0.5mm
U1: ADP5070AREZ; ETSSOP-20-1EP_4.4x6.5mm_P0.65mm_EP3x4.2mm

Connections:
/+24V: C3.1, C4.1, C5.1, D1.1 (K), D4.2 (A), J2.1, R6.1, TP11.1
/-24V: C12.2, C13.2, C14.2, D3.2 (A), D5.1 (K), J2.3, R10.2, TP24.1
GND: C1.2, C2.1, C3.2, C4.2, C5.2, C6.2, C7.2, C8.2, C9.2, C10.2, C11.2, C12.1, C13.1, C14.1, C15.2, C16.1, J1.2, J2.2, L2.2, R7.2, R8.2, R12.2, R13.1, TP15.1, U1.1 (PGND), U1.4 (SYNC/FREQ), U1.15 (AGND), U1.21 (AGND)
unnamed: C1.1, R5.2, TP9.1, U1.8 (COMP1)
unnamed: C2.2, R5.1
unnamed: C10.1, U1.16 (VREG)
unnamed: C11.1, R9.1, U1.14 (VREF)
unnamed: C15.1, R11.2, TP22.1, U1.12 (COMP2)
unnamed: C16.2, R11.1
unnamed: D1.2 (A), L1.2, TP10.1, U1.2 (SW1)
unnamed: D2.1 (K), R8.1
unnamed: D3.1 (K), L2.1, TP23.1, U1.20 (SW2)
unnamed: D4.1 (K), R12.1
unnamed: D5.2 (A), R13.2
unnamed: L1.1, TP12.1, U1.3 (INBK)
unnamed: R1.1, TP1.1
unnamed: R1.2, TP5.1
unnamed: R2.1, TP2.1
unnamed: R2.2, TP6.1
unnamed: R3.1, TP3.1
unnamed: R3.2, TP7.1
unnamed: R4.1, TP4.1
unnamed: R4.2, TP8.1
unnamed: R6.2, R7.1, TP13.1, U1.7 (FB1)
unnamed: R9.2, R10.1, TP21.1, U1.13 (FB2)
unnamed: TP18.1, U1.10 (SS)
unnamed: TP19.1, U1.6 (SLEW)
unnamed: TP20.1, U1.5 (SEQ)
VBUS: C6.1, C7.1, C8.1, C9.1, D2.2 (A), J1.1, TP14.1, U1.9 (EN1), U1.11 (EN2), U1.17 (PVIN1), U1.18 (PVINSYS), U1.19 (PVIN2)

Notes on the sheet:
POWER INPUT (5-12V)
VIN
GND
+24V
-24V
+/-24V OUTPUT (500mA MAX)
